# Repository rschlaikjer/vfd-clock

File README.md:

# VFD Clock

### Bedside clock with extended info

I'm a sucker for [old display technologies](https://github.com/rschlaikjer/ntp-nixie),
so on my arduino binge I built a bedside clock capable of displaying generic
information, with long line scrolling and whatnot. The design is fully PoE, so
the finished clock just needs one cable.

**In this repo:**
- Arduino code for the clock logic, handles fetching data from the server and VFD control.
- Eagle schematics for the clock control PCB
- Housing DXF for laser cut housing. The design is intended to be cut on a 6.7mm material.
- Server code manages actual information fetching (checking my unread mail, getting the price of bitcoin)

## Partlist
- Atmega 328P (along with 16MHz crystal, 2x 22pf caps)
- Silvertel A9700 PoE module
- ENC28J60 ethernet PHY
- RB1-125BHQ1A RJ45 jack with magnetics
- LM1117 3.3V regulator (for ENC28J60)
- VFD with serial interface (Here I'm using a Noritake CU20045SCPB-T31A)

## Pretty pictures

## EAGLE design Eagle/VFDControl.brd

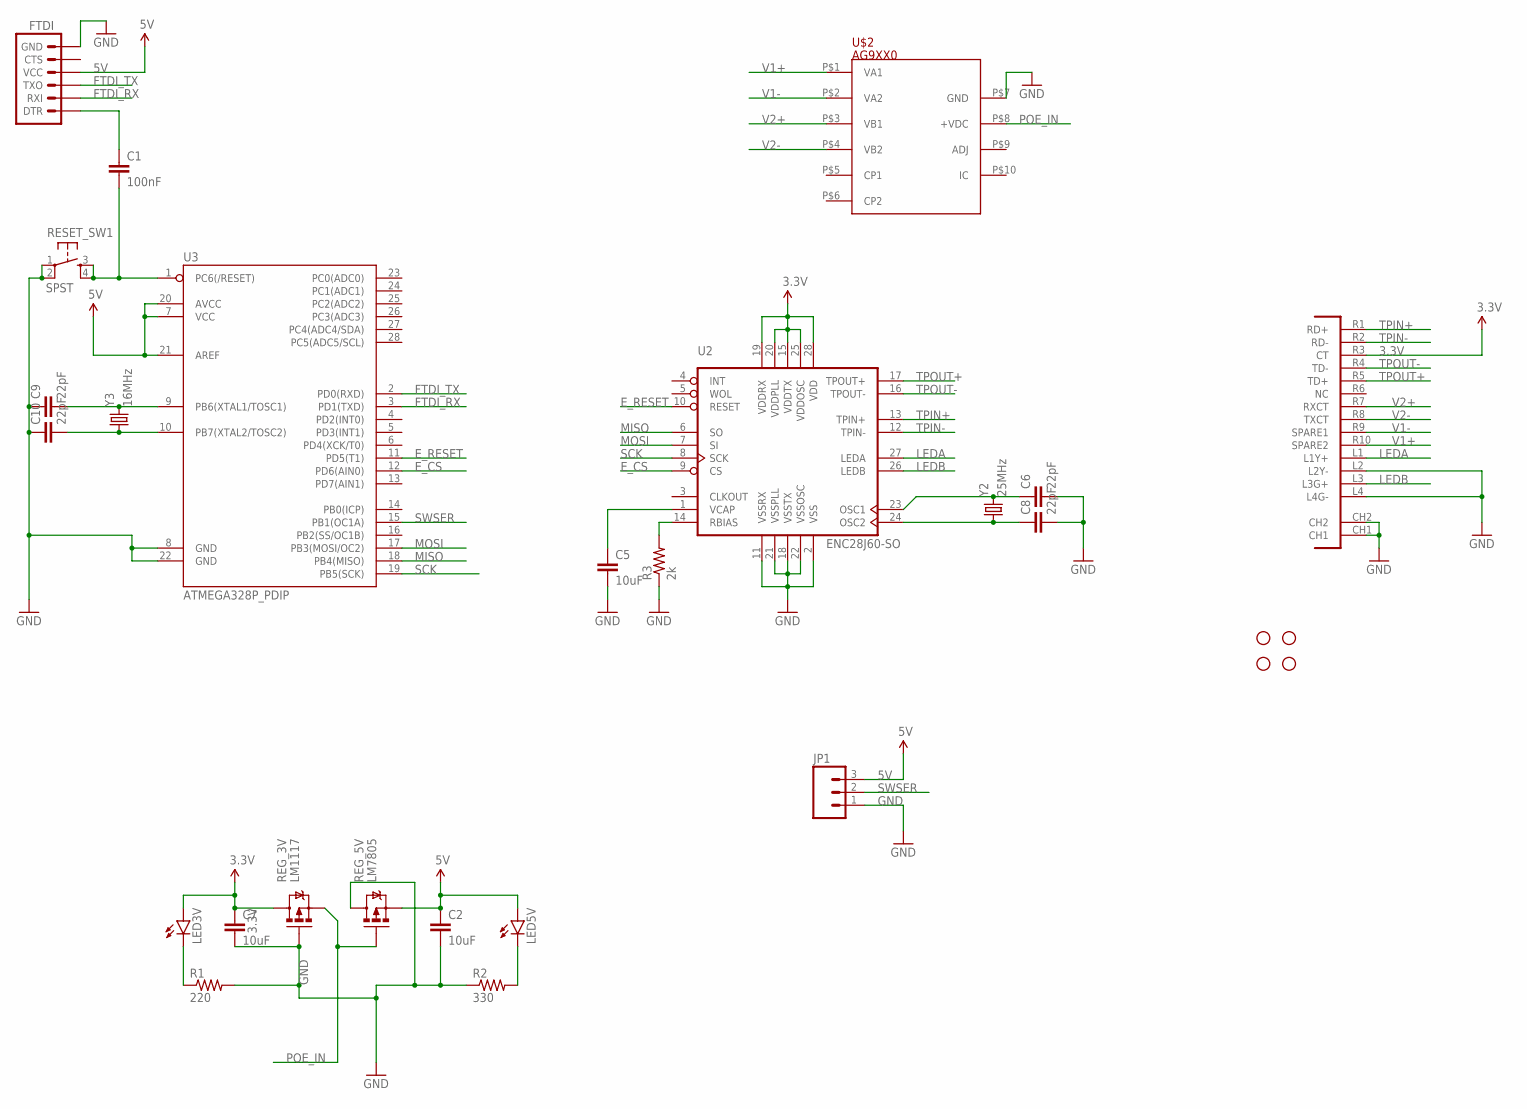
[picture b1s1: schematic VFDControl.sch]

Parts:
C1: 100nF; CAP-PTH-SMALL
C2, C5, C7: 10uF; CAP-PTH-SMALL
C6, C8, C9, C10: 22pF; CAP-PTH-SMALL
FTDI: ARDUINO_SERIAL_PROGRAMPTH; 1X06
JP1: M03PTH; 1X03
LED3V, LED5V: LED3MM
R1: 220; AXIAL-0.1
R2: 330; AXIAL-0.1
R3: 2k; AXIAL-0.1
REG_3V: LM1117; TO220V
REG_5V: LM7805; TO220V
RESET_SW1: SPST; TAC-SWITCH-PTH
STANDOFF1, STANDOFF2, STANDOFF3, STANDOFF4: STAND-OFF
U2: ENC28J60-SO; SO28W
U3: ATMEGA328P_PDIP; DIL28-3
U$2: AG9XX0; AG9000
U$3: POE-RJ45
Y2: 25MHz; HC49US
Y3: 16MHz; HC49US

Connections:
3.3V: C7.1, LED3V.A, REG_3V.2 (D), U2.15 (VDDTX), U2.19 (VDDRX), U2.20 (VDDPLL), U2.25 (VDDOSC), U2.28 (VDD), U$3.R3 (CT)
5V: C2.1, FTDI.4 (VCC), JP1.3, LED5V.A, REG_5V.3 (S), U3.7 (VCC), U3.20 (AVCC), U3.21 (AREF)
E_CS: U2.9 (CS), U3.12 (PD6(AIN0))
E_RESET: U2.10 (RESET), U3.11 (PD5(T1))
FTDI_RX: FTDI.2 (RXI), U3.3 (PD1(TXD))
FTDI_TX: FTDI.3 (TXO), U3.2 (PD0(RXD))
GND: C2.2, C5.2, C6.2, C7.2, C8.2, C9.1, C10.1, FTDI.6 (GND), JP1.1, R1.P$2 (2), R2.P$1 (1), R3.P$1 (1), REG_3V.1 (G), REG_5V.2 (D), RESET_SW1.1, RESET_SW1.2, U2.2 (VSS), U2.11 (VSSRX), U2.18 (VSSTX), U2.21 (VSSPLL), U2.22 (VSSOSC), U3.8 (GND), U3.22 (GND), U$2.P$7 (GND), U$3.CH1, U$3.CH2, U$3.L2 (L2Y-), U$3.L4 (L4G-)
LEDA: U2.27 (LEDA), U$3.L1 (L1Y+)
LEDB: U2.26 (LEDB), U$3.L3 (L3G+)
MISO: U2.6 (SO), U3.18 (PB4(MISO))
MOSI: U2.7 (SI), U3.17 (PB3(MOSI/OC2))
unnamed: LED3V.K (C), R1.P$1 (1)
unnamed: LED5V.K (C), R2.P$2 (2)
unnamed: R3.P$2 (2), U2.14 (RBIAS)
unnamed: C5.1, U2.1 (VCAP)
unnamed: C6.1, U2.23 (OSC1), Y2.2
unnamed: C8.1, U2.24 (OSC2), Y2.1
unnamed: C9.2, U3.9 (PB6(XTAL1/TOSC1)), Y3.2
unnamed: C10.2, U3.10 (PB7(XTAL2/TOSC2)), Y3.1
unnamed: C1.1, FTDI.1 (DTR)
POE_IN: REG_3V.3 (S), REG_5V.1 (G), U$2.P$8 (+VDC)
RESET: C1.2, RESET_SW1.3, RESET_SW1.4, U3.1 (PC6(/RESET))
SCK: U2.8 (SCK), U3.19 (PB5(SCK))
SWSER: JP1.2, U3.15 (PB1(OC1A))
TPIN+: U2.13 (TPIN+), U$3.R1 (RD+)
TPIN-: U2.12 (TPIN-), U$3.R2 (RD-)
TPOUT+: U2.17 (TPOUT+), U$3.R5 (TD+)
TPOUT-: U2.16 (TPOUT-), U$3.R4 (TD-)
V1+: U$2.P$1 (VA1), U$3.R10 (SPARE2)
V1-: U$2.P$2 (VA2), U$3.R9 (SPARE1)
V2+: U$2.P$3 (VB1), U$3.R7 (RXCT)
V2-: U$2.P$4 (VB2), U$3.R8 (TXCT)

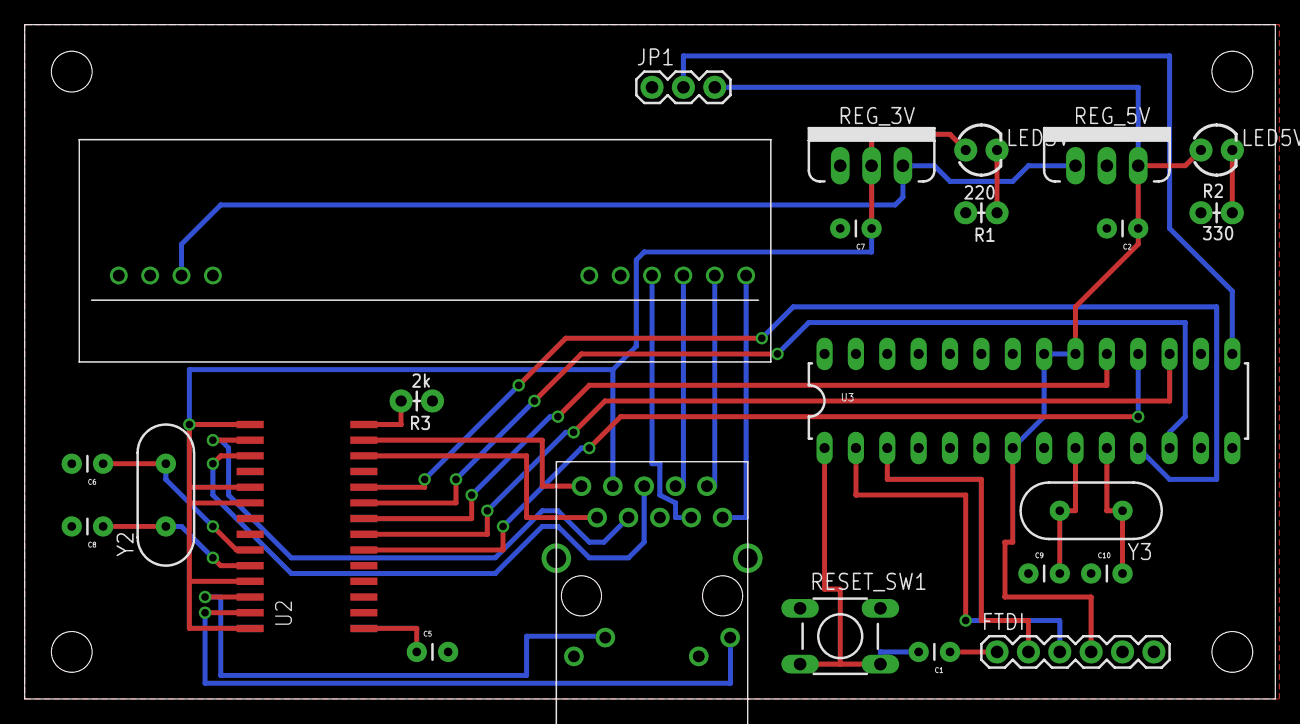
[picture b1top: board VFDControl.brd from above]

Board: 2 copper layers, 101.3 x 54.6 mm, 28 parts (0 on the bottom side), 32 nets.

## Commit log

2015-04-09 Include sources
2015-04-09 Add dxf for housing
2015-04-09 Add readme

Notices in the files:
parts and their libraries:
SparkFun-Capacitors: Licensing: Creative Commons ShareAlike 4.0 International - https://creativecommons.org/licenses/by-sa/4.0
